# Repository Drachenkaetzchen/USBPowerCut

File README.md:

# USB Power Cut

A small PCB to control power to a USB device. I've designed this in order to be able to cut power to a
[HDMI display](https://www.aliexpress.com/item/32889893278.html) when it's not in use, for example, via a Raspberry Pi.

# Specifications

- MicroUSB input
- USB Type A output
- Maximum permissible USB current draw: 1A
- JST XH to control the power. Control voltage 3.3V or 5V.
- Active power consumption 35mA (only when switched on)

# Known Issues

- One mounting hole is offset to the right by 0.5mm, the DIN mounting adapter is adjusted for that.

# BOM

| Designator| Part
| ----------|--------------------
| D1 | 1N4148 DO35-10                   
| K1 | V23079-A1011-B301                   
| Q1 | 2N7002 SOT23                     
| R1 | 100k 0805                     
| X1 | JST XH 2 pin
| X2 | AMP 787616-1                       
| X3 | 10104110-0001LF                 

# FAQ

**Why a relay?**

I didn't have any P-channel mosfets in stock, but plenty of those small relays, so that's why I based my design around
them. I rather use components I have in stock than to order new ones.

N-channel mosfets shouldn't be used to control USB power due to possible leakage over the data lines.

**Why not use the RPI4 USB power control functionality?**

On a Raspberry Pi 4, this cuts power to all USB ports. In my case, I only want the display to be turned off. All other
ports should remain on.

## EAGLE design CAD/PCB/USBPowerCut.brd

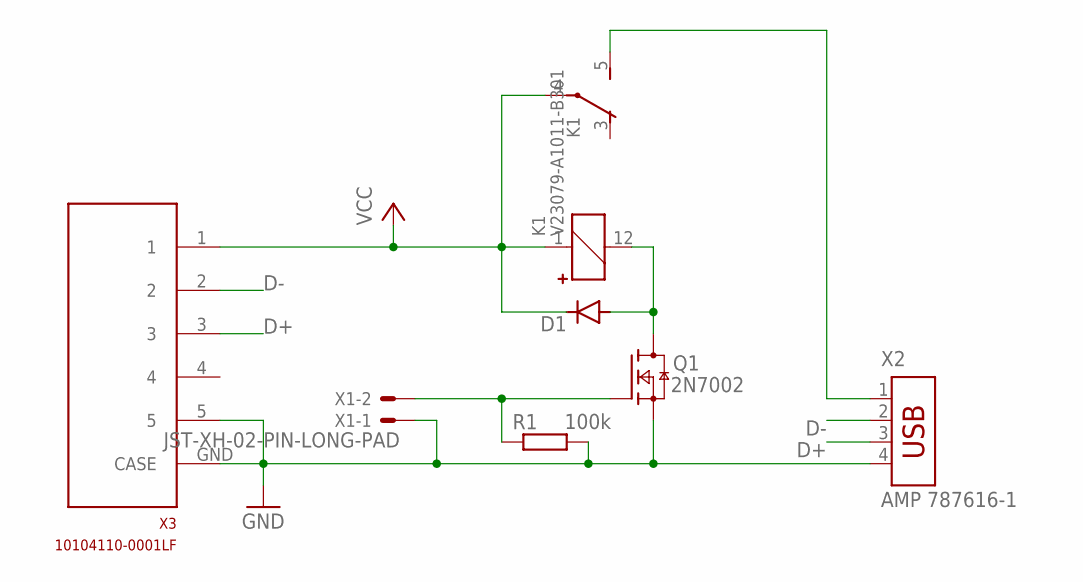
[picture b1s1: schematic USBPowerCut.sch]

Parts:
D1: 1N4148; DO35-10
K1: V23079-A1011-B301; V23079A
Q1: 2N7002; SOT23
R1: 100k; R0805
X1: JST-XH-02-PIN-LONG-PAD; JST-XH-02-PACKAGE-LONG-PAD
X2: AMP 787616-1; USB
X3: 10104110-0001LF; MICRO_USB

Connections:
D+: X2.3, X3.3
D-: X2.2, X3.2
GND: Q1.2 (S), R1.2, X1.1, X2.4, X3.5, X3.GND (CASE)
unnamed: D1.A, K1.12 (-), Q1.3 (D)
unnamed: K1.5 (S), X2.1
unnamed: Q1.1 (G), R1.1, X1.2
VCC: D1.C, K1.1 (+), K1.4, X3.1

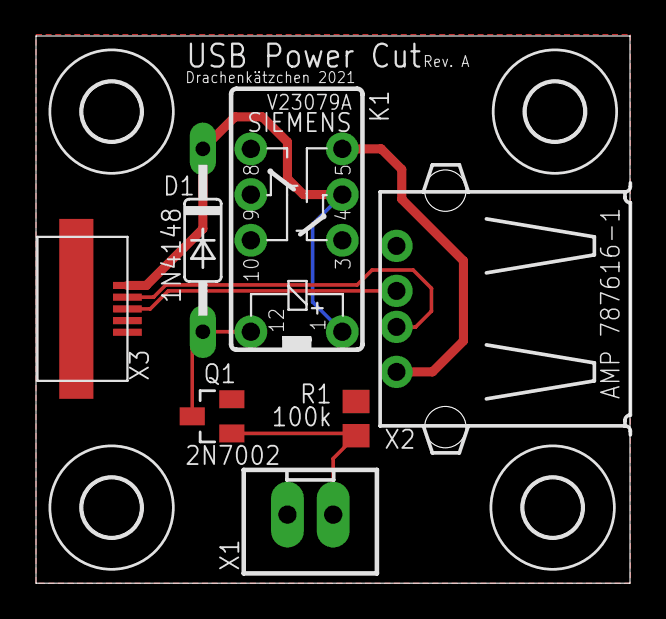
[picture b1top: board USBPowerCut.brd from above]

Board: 2 copper layers, 33.0 x 30.4 mm, 11 parts (0 on the bottom side), 7 nets.

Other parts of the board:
U$1, U$2, U$3, U$4: 3,2

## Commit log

2021-10-18 Clarified that the data lines are passed through
2025-02-01 Prepare repo for V2
2025-03-20 Updated docs
